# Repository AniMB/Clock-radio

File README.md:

# ⏰ Clock Radio – MicroPython Smart Clock System

**`mi69.py`** is the main script of an embedded, Wi-Fi-enabled FM radio and smart clock interface built on **MicroPython**. It combines a **real-time clock**, **OLED UI**, **FM tuner**, and **web connectivity** into a single-threaded yet responsive application, suitable for microcontrollers like the Raspberry Pi Pico W.

---

## 🚦 Architecture Overview

```
             ┌────────────┐
             │   Button   │◄────────────┐
             └────┬───────┘             │
                  ▼                     │
             ┌─────────────┐     Debounce, Hold Detection
             │    Main     │─────────────┘
             │   (mi69.py) │
             └────┬────────┘
        ┌─────────┴─────────┐
        ▼                   ▼
┌────────────┐       ┌────────────┐
│  Display   │       │   Radio    │
│ (OLED + UI)│       │  (FM chip) │
└────┬───────┘       └────┬───────┘
     ▼                    ▼
 ┌──────────┐      ┌────────────┐
 │ Web Time │      │ Web Server │◄──── Access via browser
 └──────────┘      └────────────┘
```

---

## 🧠 Code Modules

### `mi69.py` – Main Control Loop

- Initializes components (RTC, FM radio, OLED, Button, Web).
- Sets up **interrupt-safe button handling** (short vs. long press).
- Periodically updates:
  - Display (clock, station, volume)
  - State file (`web_data.json`)
- Starts the **HTTP server in a separate thread**.

#### Core Mechanics

- `oled_dirty`, `json_dirty` flags minimize redundant writes
- `utime.ticks_ms()` is used to throttle updates
- JSON I/O and OLED are **locked via a thread-safe `_lock`**
- Long press (>3 sec) and debounce logic built-in

---

### `libraries/display.py` – OLED Drawing

Encapsulates all drawing on the OLED display using `framebuf`:

- `display_clock_time(rtc.datetime())`
- `display_radio_freq(101.9)`
- `display_volume(5)`

Also handles font scaling, screen clearing, and line placement.

---

### `libraries/radio.py` – FM Radio Control

Controls an FM tuner (likely via I2C/SPI). Key methods:

- `set_freq(freq)`: set frequency (MHz)
- `seek_up() / seek_down()`: scan for stations
- `set_volume(level)`: 0–15 volume levels

Keeps state internally for restoring or syncing with UI/web.

---

### `config/resources.py` – Global Shared State

Contains:

- Button pin definitions
- Flags: `oled_dirty`, `json_dirty`, `btn_short_req`, etc.
- Constants: debounce delay, hold time threshold
- A global `_lock` used by both threads

This is the “RAM” for the system shared across all modules.

---

### `web_connectivity/web.py` – HTTP Server

A simple HTTP server that runs on a new thread:

- Serves a web interface (to be extended)
- API routes:
  - `GET /status`: Return JSON state
  - `POST /set_time`, `POST /set_volume`, etc.
- Reads/writes `web_data.json` using the shared `_lock`

This lets users control and monitor the device remotely.

---

### `web_data.json` – State File

JSON-encoded structure for UI and web server to share state.

```json
{
  "volume": 5,
  "frequency": 101.9,
  "time": "12:34:56",
  "alarm_enabled": false
}
```

Used for persistence and as a synchronization bridge.

---

## 🧵 Concurrency & Thread Safety

- Uses MicroPython’s `_thread` module for background web server
- Ensures safety via `_lock` for:
  - JSON file access
  - OLED updates

```python
from _thread import start_new_thread
start_new_thread(WebServer().start, ())
```

---

## 🔋 Efficiency Considerations

- OLED and JSON updates are **rate-limited** using `ticks_ms()`
- Button reads are **debounced**
- Threads are **lightweight**, preventing blocking I/O
- Display refreshes only on changes

---

## 🚀 Future Extensions

- 📆 Alarm scheduling + snooze logic
- 🌐 NTP time sync
- 📱 Better web UI with sliders & buttons
- 📻 Station presets & memory
- 🔌 BLE or MQTT integration

---

## 📎 Developer Notes

- Clear modularity: `main`, `display`, `radio`, `web`, `resources`
- Code follows **embedded-safe design** (no dynamic memory abuse)
- Minimal, fast and effective for real-time low-power devices

---

## 🧠 Summary

This project is a highly educational template for combining hardware control, UI, web connectivity, and concurrency in **MicroPython**. It’s a complete working system for embedded devices with many real-world use cases.

---

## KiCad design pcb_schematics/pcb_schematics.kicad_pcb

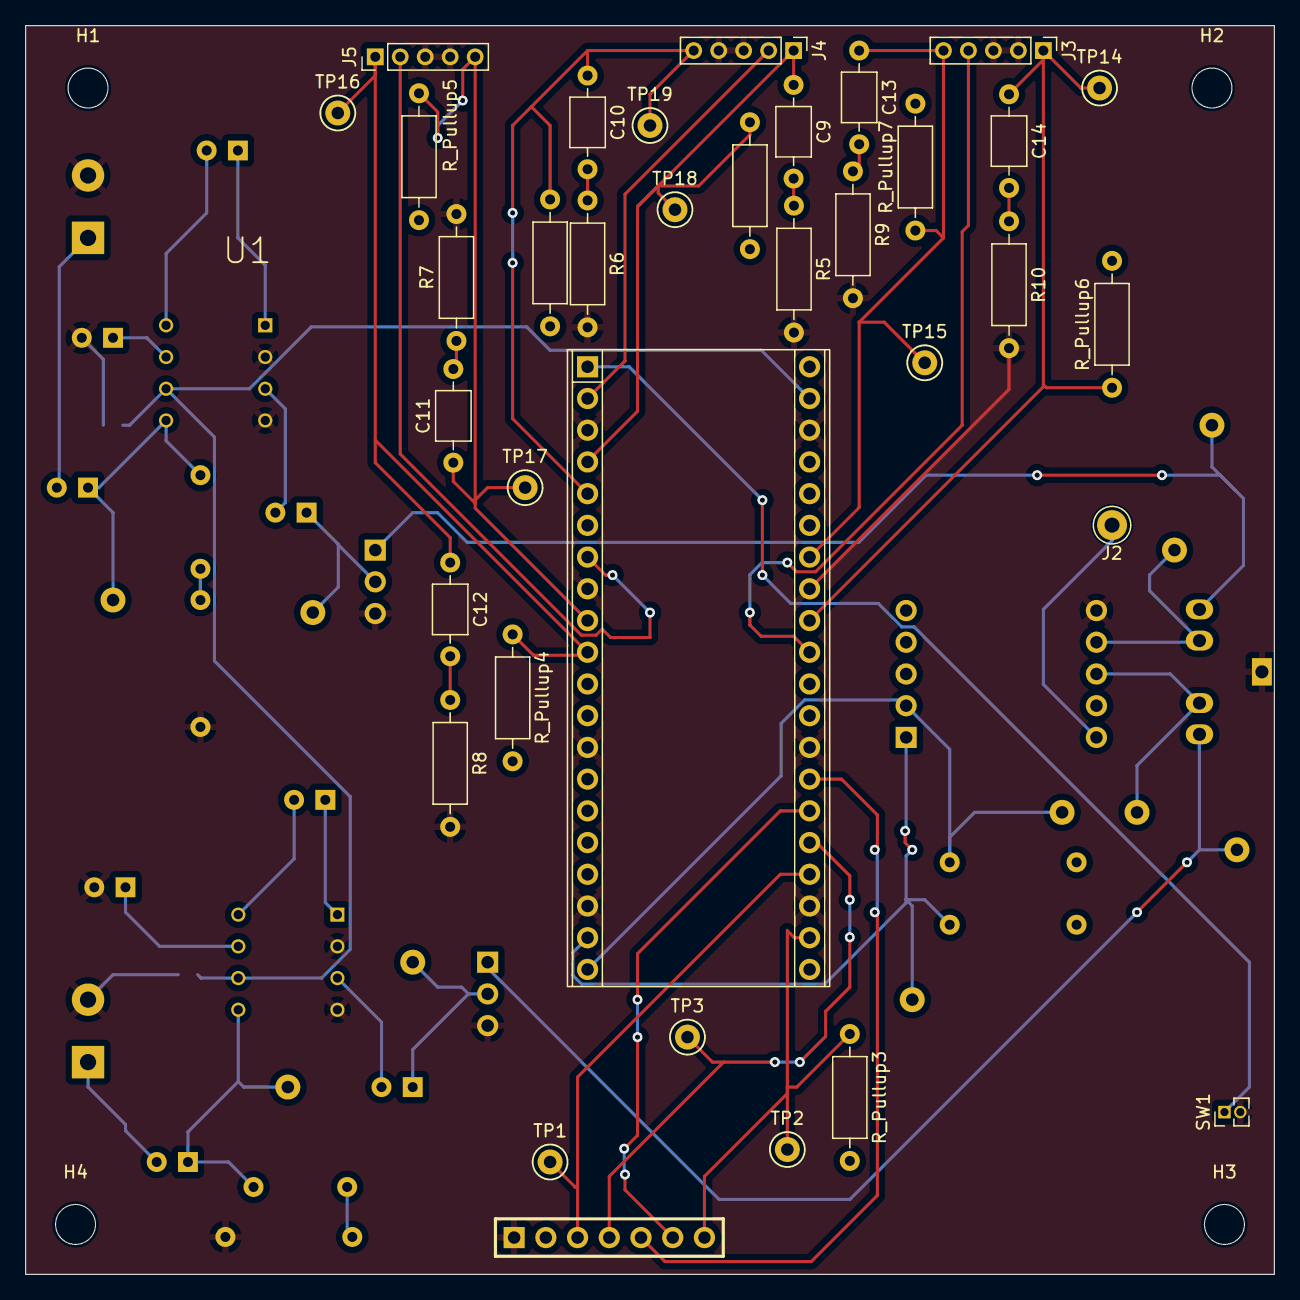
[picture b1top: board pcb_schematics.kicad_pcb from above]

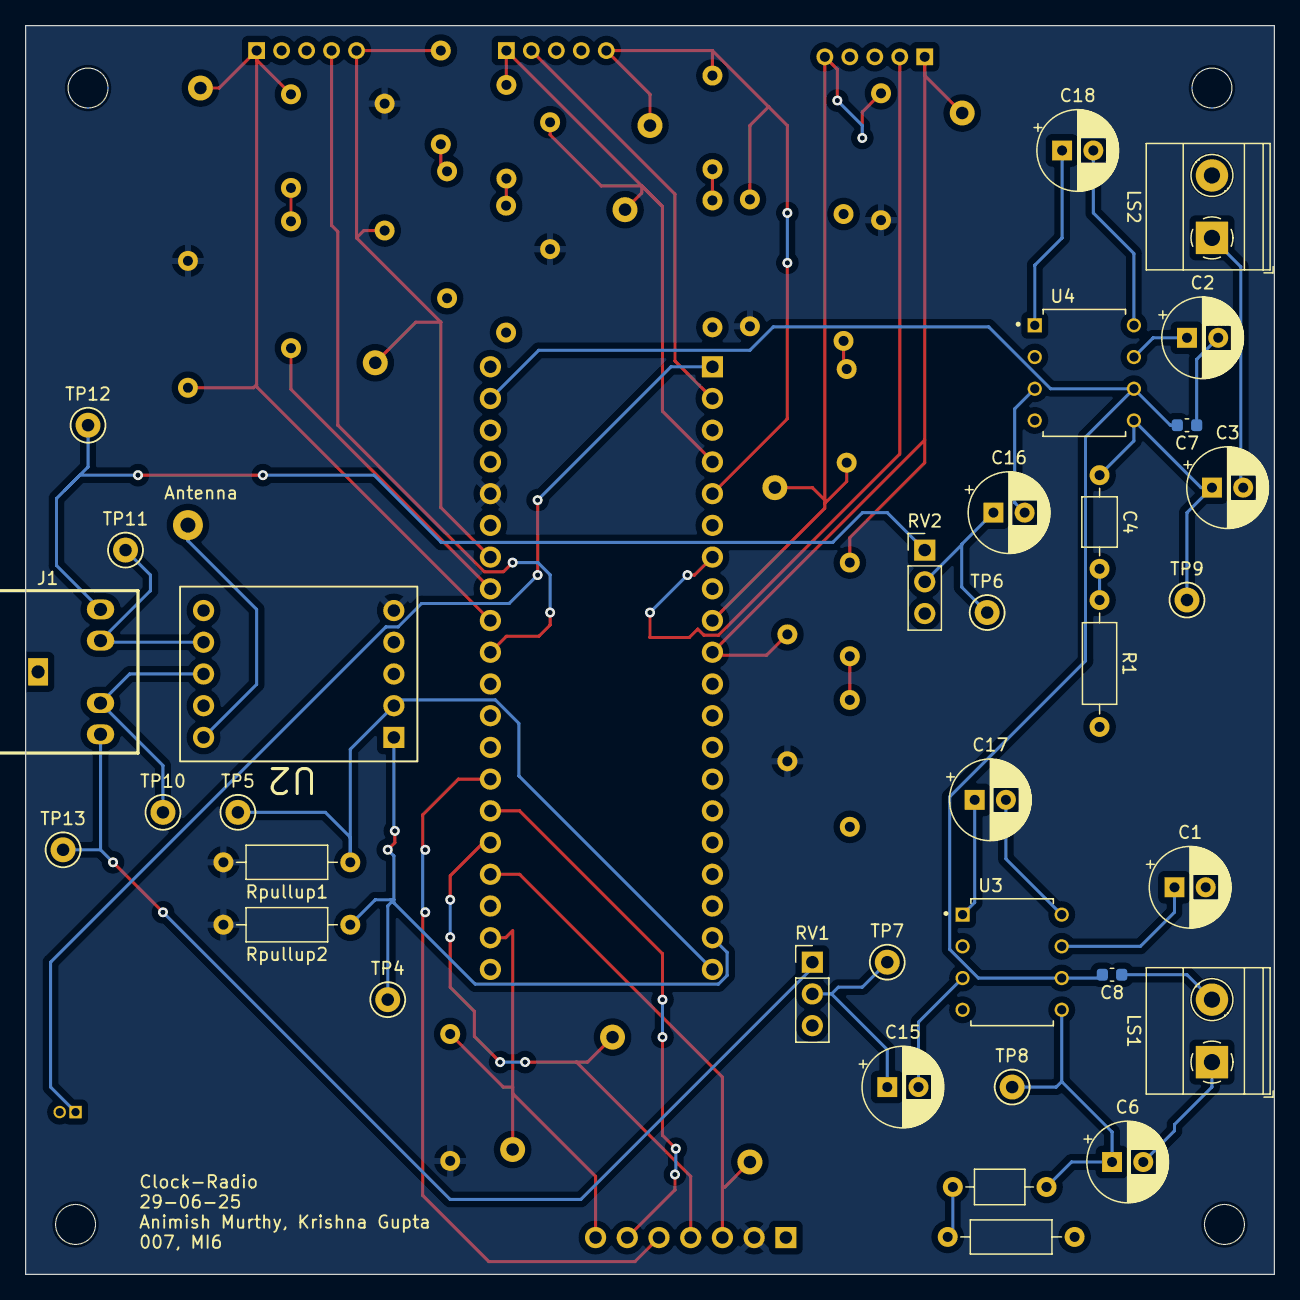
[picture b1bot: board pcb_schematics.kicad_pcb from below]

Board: 2 copper layers, 100.0 x 100.0 mm, 73 parts (34 on the bottom side), 47 nets.

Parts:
C1, C2, C17, C18: 10 µF; CP_Radial_D6.3mm_P2.50mm
C3, C6, C15, C16: 470 µF; CP_Radial_D6.3mm_P2.50mm
C4, C5, C9, C10, C11, C12, C13, C14: 0.05 µF; C_Axial_L3.8mm_D2.6mm_P7.50mm_Horizontal
C7, C8: 0.1 µF; C_0603_1608Metric
DISP1: OLED Display; OLED_Display_1.3
H1, H2, H3, H4: MountingHole; MountingHole_3.2mm_M3
J1: CUE_SJ1-352XNG
J2: Conn_01x01_Pin; Pin_D1.0mm_L10.0mm_LooseFit
J3, J4, J5: Conn_01x05; PinHeader_1x05_P2.00mm_Vertical
LS1, LS2: Speaker; TerminalBlock_Phoenix_MKDS-1,5-2_1x02_P5.00mm_Horizontal
R1, R2, R5, R6, R7, R8, R9, R10: 10Ω; R_Axial_DIN0207_L6.3mm_D2.5mm_P10.16mm_Horizontal
RV1, RV2: 10kΩ; PinHeader_1x03_P2.54mm_Vertical
R_Pullup1, R_Pullup2, R_Pullup3, R_Pullup4, R_Pullup5, R_Pullup6, R_Pullup7: 2kΩ; R_Axial_DIN0207_L6.3mm_D2.5mm_P10.16mm_Horizontal
Rpullup1, Rpullup2: 2k; R_Axial_DIN0207_L6.3mm_D2.5mm_P10.16mm_Horizontal
SW1: SW_Push; PinHeader_1x02_P1.27mm_Vertical
TP1, TP2, TP3, TP4, TP5, TP6, TP7, TP8, TP9, TP10, TP11, TP12, TP13, TP14, TP15, TP16, TP17, TP18, TP19: TestPoint; TestPoint_Keystone_5000-5004_Miniature
U1: RPi_Pico_TH
U2: RDA5807M_Module; RDA5807M_Module_TH
U3, U4: LM386; DIP794W45P254L1016H508Q8

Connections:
5V: C7.2, C8.2, U1.39 (VSYS), U3.6 (V+), U4.6 (V+)
/3V3: DISP1.2 (VDD), R_Pullup1.2, R_Pullup2.2, R_Pullup3.2, R_Pullup4.2, R_Pullup5.2, R_Pullup6.2, R_Pullup7.2, Rpullup1.2, Rpullup2.2, U1.36 (3V3), U2.5 (VDD)
/CS: DISP1.7 (CS), R_Pullup3.1, TP2.1, U1.22 (GP17)
/DC: DISP1.6 (DC), U1.26 (GP20)
/I2CSCK: Rpullup1.1, TP5.1, U1.20 (GP15), U2.2 (SCLK)
/I2CTX: Rpullup2.1, TP4.1, U1.19 (GP14), U2.1 (SDIO)
/LOUT: J1.5 (Ring_Switch), TP10.1, U2.8 (LOUT)
/LSpeaker: J1.3 (Tip), RV1.1, TP13.1
/RES: DISP1.5 (RES), U1.27 (GP21)
/ROT1A: C10.1, J4.5, R_Pullup2.1, TP19.1, U1.5 (GP3)
/ROT1B: C9.1, J4.1, R_Pullup1.1, TP18.1, U1.4 (GP2)
/ROT2A: C11.1, J5.5, R_Pullup5.1, TP17.1, U1.9 (GP6)
/ROT2B: C12.1, J5.1, R_Pullup4.1, TP16.1, U1.10 (GP7)
/ROT3A: C13.1, J3.5, R_Pullup7.1, TP15.1, U1.34 (GP28/ADC2)
/ROT3B: C14.1, J3.1, R_Pullup6.1, TP14.1, U1.32 (GP27/ADC1)
/ROUT: J1.4 (Tip_Switch), TP11.1, U2.7 (ROUT)
/RSpeaker: J1.2 (Tip), RV2.1, TP12.1
/SCK: DISP1.3 (SCLK), TP1.1, U1.24 (GP18)
/SDA: DISP1.4 (SDA), TP3.1, U1.25 (GP19)
/SW1: SW1.1, U1.1 (GP0)
/SW2: J4.2, U1.2 (GP1)
/SW3: J3.4, U1.31 (GP26/ADC0)
/SW4: J5.2, U1.7 (GP5)
GND: C1.2, C2.2, C7.1, C8.1, DISP1.1 (VSS/GND), J1.1 (Sleeve), J3.2, J3.3, J4.3, J4.4, J5.3, J5.4, LS1.2, LS2.2, R1.2, R2.2, R5.2, R6.2, R7.2, R8.2, R9.2, R10.2, RV1.3, RV2.3, SW1.2, U1.3 (GND), U1.8 (GND), U1.13 (GND), U1.18 (GND), U1.23 (GND), U1.28 (GND), U1.33 (GND), U1.38 (GND), U2.6 (GND), U3.2 (-), U3.4 (GND), U4.2 (-), U4.4 (GND)
unnamed: C3.1, C4.1, TP9.1, U4.5
unnamed: C3.2, LS2.1
unnamed: C4.2, R1.1
unnamed: C5.1, C6.1, TP8.1, U3.5
unnamed: C5.2, R2.1
unnamed: C6.2, LS1.1
unnamed: C9.2, R5.1
unnamed: C10.2, R6.1
unnamed: C11.2, R7.1
unnamed: C12.2, R8.1
unnamed: C13.2, R9.1
unnamed: C14.2, R10.1
unnamed: C15.1, RV1.2, TP7.1
unnamed: C16.1, RV2.2, TP6.1
unnamed: C17.1, U3.1 (GAIN)
unnamed: C17.2, U3.8 (GAIN)
unnamed: C18.1, U4.1 (GAIN)
unnamed: C18.2, U4.8 (GAIN)
unnamed: J2.1, U2.10 (FMIN)
unnamed: C15.2, U3.3 (+)
unnamed: C1.1, U3.7 (BYPASS)
unnamed: C16.2, U4.3 (+)
unnamed: C2.1, U4.7 (BYPASS)

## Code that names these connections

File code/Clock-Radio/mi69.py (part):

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# ]

# Rotary Encoder 1 Pins (connected to GP2, GP3, GP1)
encoder1A = Pin(3, Pin.IN, Pin.PULL_UP)    # ROT1A
encoder1B = Pin(2, Pin.IN, Pin.PULL_UP)    # ROT1B
encoder2SW = Pin(1, Pin.IN, Pin.PULL_UP)   # SW2

# Encoder 2 Pins (J5) mapped to GP4, GP5, GP6
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encoder4SW = Pin(5, Pin.IN, Pin.PULL_UP)   # SW4

# Rotary Encoder 3 Pins (connected to GP26, GP27, GP28)
encoder3A = Pin(28, Pin.IN, Pin.PULL_UP)   # ROT3A
encoder3B = Pin(27, Pin.IN, Pin.PULL_UP)   # ROT3B
encoder3SW = Pin(26, Pin.IN, Pin.PULL_UP)  # SW3


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# ——— Hardware Initialization ———
rtc = RTC()
spi = SPI(0, sck=Pin(18), mosi=Pin(19), baudrate=100000)
oled = SSD1306_SPI(128, 64, spi, dc=Pin(20), res=Pin(21), cs=Pin(17), reset=True)



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
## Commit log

2025-06-04 Lab2 and micropython setup
2025-06-11 Adds radio and webpage
2025-06-11 fixes Radio
2025-06-12 Fixed code to increase volume in fm_radio.py
2025-06-27 Adding PCB schematics
2025-06-28 Converted to connectors
2025-06-29 Updates PCb according to ROB's feedback
    Added PCb layour according to the discussion with butoons and display on top and display below using front copper. Added Radio module using back copper. Speakers left to set up using back copper.
2025-06-29 compeltes PCB
    Only the DRC has a couple errors
2025-06-29 Updates footprints in schematic
2025-06-29 Fixes errors in DRC
    Adds SMD capacitors too
2025-06-29 Runs DRC and ERC again
2025-06-30 Accomodating usb cable
2025-07-04 Revision 3
    Changed the amplifier and the rotary encoder schemtic. Needs work on pcb
2025-07-05 completes third version of PCB
2025-07-07 fixed issues mentioned by rob and brent
    Fix iteration 1
2025-07-08 made changes based on changes requested
    Fix iteration 2
2025-07-09 Submitted to JLCPCB
    Modification with pcb_schematics being the final version.
2025-07-13 Added WBS.drawio
2025-07-13 Finished first iteration of WBS
2025-07-13 Adds Ganntt chart
2025-07-13 Pcb (#1)
    * Converted to connectors
    * Updates PCb according to ROB's feedback
    Added PCb layour according to the discussion with butoons and display on top and display below using front copper. Added Radio module using back copper. Speakers left to set up using back copper.
    * compeltes PCB
    Only the DRC has a couple errors
    * Updates footprints in schematic
2025-07-13 cleans the code
2025-07-13 Pm (#3)
    * Converted to connectors
    * Updates PCb according to ROB's feedback
    Added PCb layour according to the discussion with butoons and display on top and display below using front copper. Added Radio module using back copper. Speakers left to set up using back copper.
    * compeltes PCB
    Only the DRC has a couple errors
    * Updates footprints in schematic
2025-07-16 Adds web.py and structures the code
2025-07-21 restructures code
2025-07-21 modifies structure
2025-07-21 Fixes the web.py.
    Needs a webpage and a js file
2025-07-21 modified the webpage and set up the main files
2025-07-22 Completes website and runs informal tests
    completes website code development
    updated choice in radio
2025-07-24 updates the jsonhandler
2025-07-25 makes a connection but js fails to load
2025-07-25 bob and vagana
2025-07-26 sendall fix
2025-07-26 some more inconsistencies
2025-07-26 Changes method to access obj
2025-07-26 FIxed import and blocking errors
2025-07-27 fixes errors and allows entire request to be processed
2025-07-27 Display's time from the website in 24 hour and 12 hours. Completes test plan
2025-07-27 fixes AM PM
2025-07-28 completes radio tests
2025-07-29 updated clock mode
2025-07-29 updated alarm mode
2025-07-29 completes handle referesh
2025-07-29 radio module updated with repr function
2025-07-29 good to review
2025-07-29 added FM mode and minor updates
2025-07-29 minor updates
2025-07-29 3rd try
2025-07-29 using inheritance
2025-07-29 review required
2025-07-29 dictionary added and updates
2025-07-29 boba vanga
2025-07-29 looked for edge cases
2025-07-29 2nd try
2025-07-29 added snooze and minor updates
2025-07-29 added volume module
2025-07-29 reduce redudancy and fixed issue
2025-07-29 changed idle mode
2025-07-29 chnages and rebases code to newer verisons
2025-07-29 Creates major chnages
    Requires work to be done of alarm. THen to work on radio alarm button
2025-07-29 pushes major code updates
2025-07-29 fixes bugs and adds time
2025-07-29 pushing fixes
2025-07-29 made massive changes
2025-07-30 Most working code
2025-07-30 Completes the code with locked visible
2025-07-30 Fixed comment and addds rtc time
2025-07-30 Revert "Completes the code with locked visible"
    This reverts commit 778d3d012da1678581d6e8521fdcfdb85e9801f0.
2025-07-30 Revert "Fixed comment and addds rtc time"
    This reverts commit 116130d8c3e0ab863ebd2706c4f76c6ead57e4d2.
2025-07-30 Reapply "Completes the code with locked visible"
    This reverts commit 0901dce5da3b9b6a84a9f30ec13ec27c314d50b2.
2025-07-31 Resolves COmment
2025-08-05 Cleaing code
2025-08-06 Completes the readme
